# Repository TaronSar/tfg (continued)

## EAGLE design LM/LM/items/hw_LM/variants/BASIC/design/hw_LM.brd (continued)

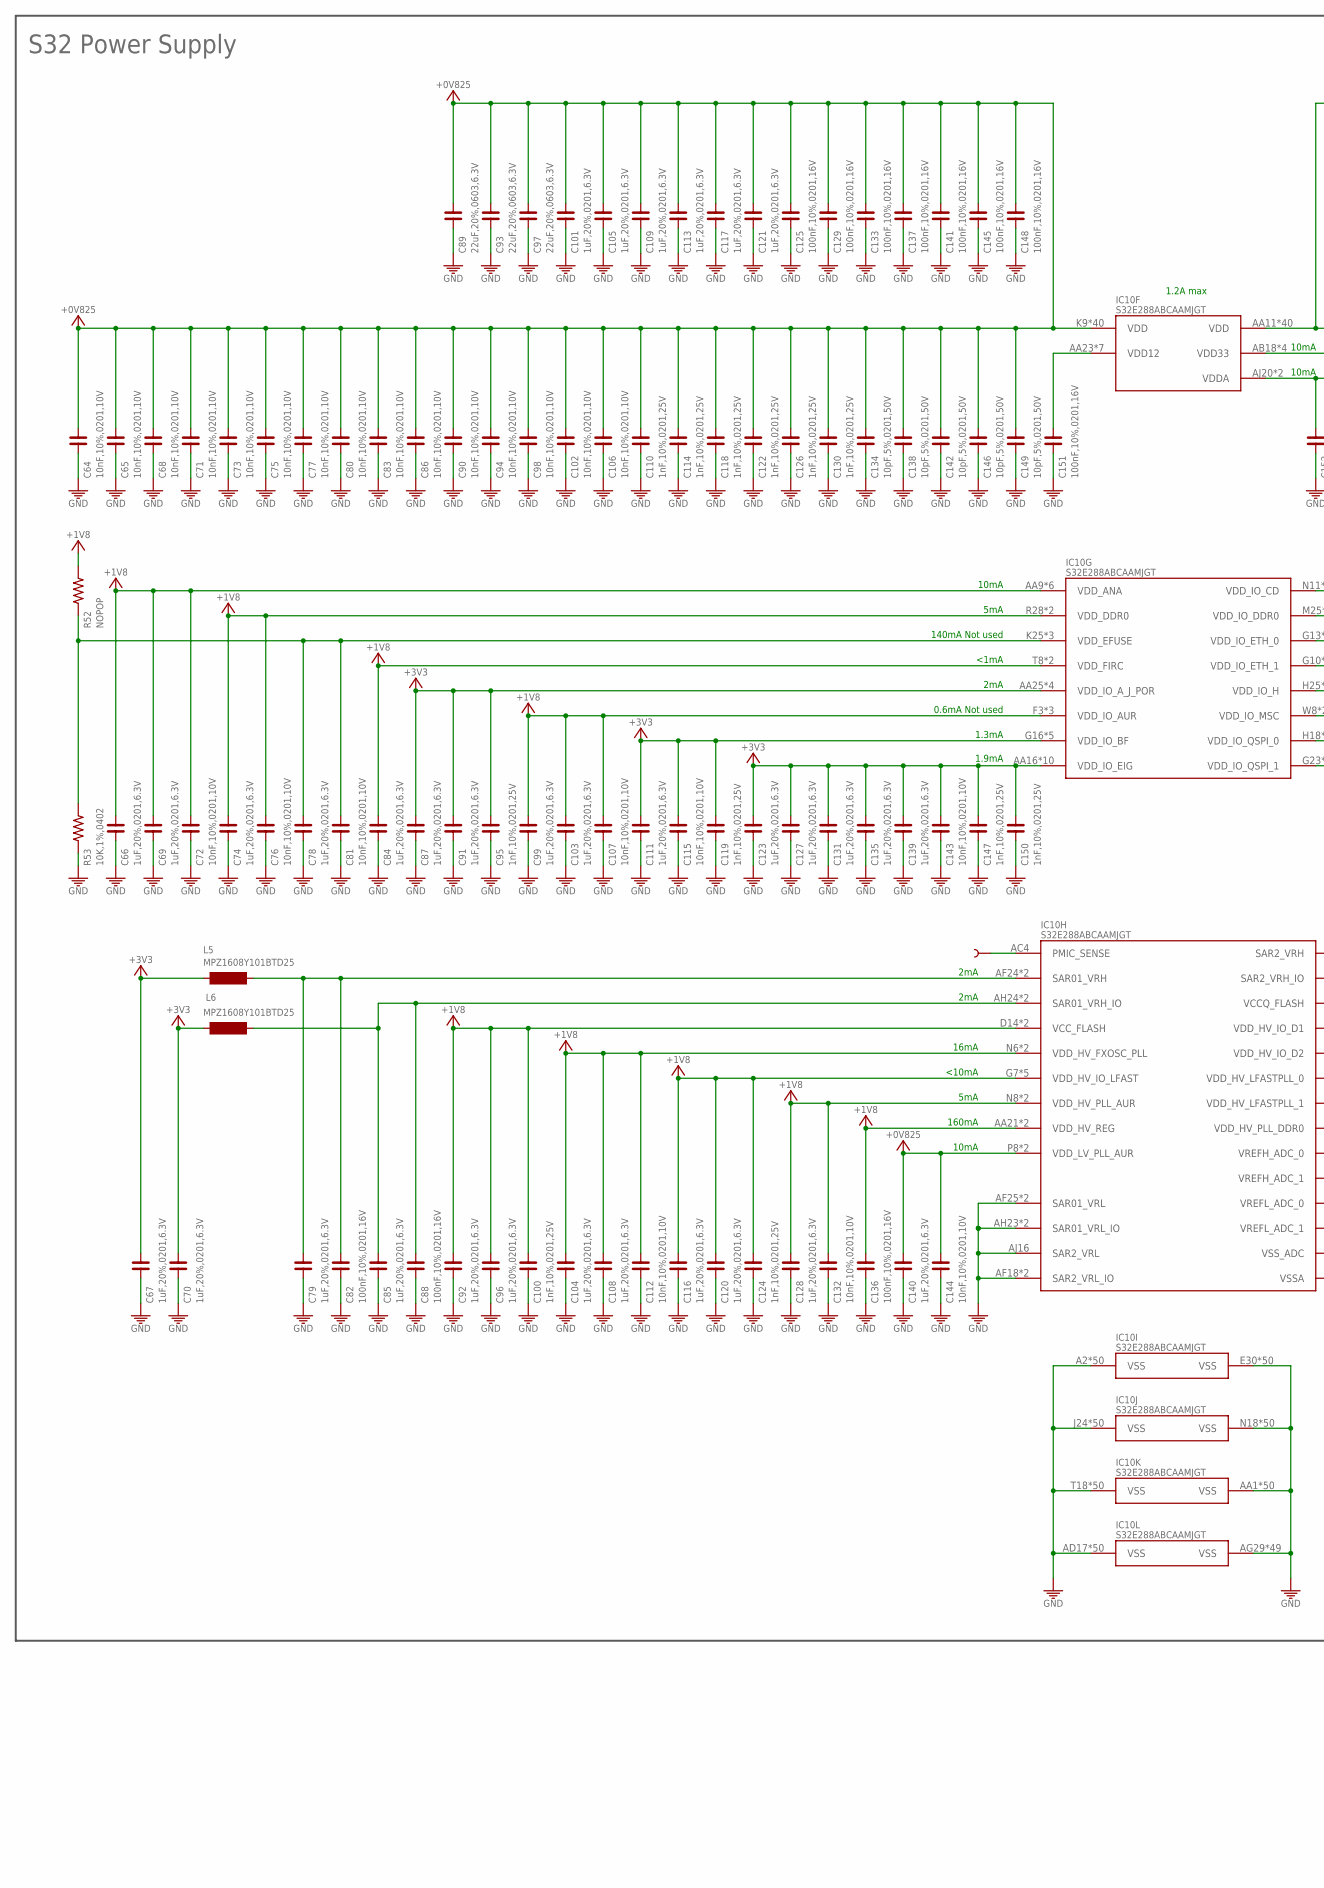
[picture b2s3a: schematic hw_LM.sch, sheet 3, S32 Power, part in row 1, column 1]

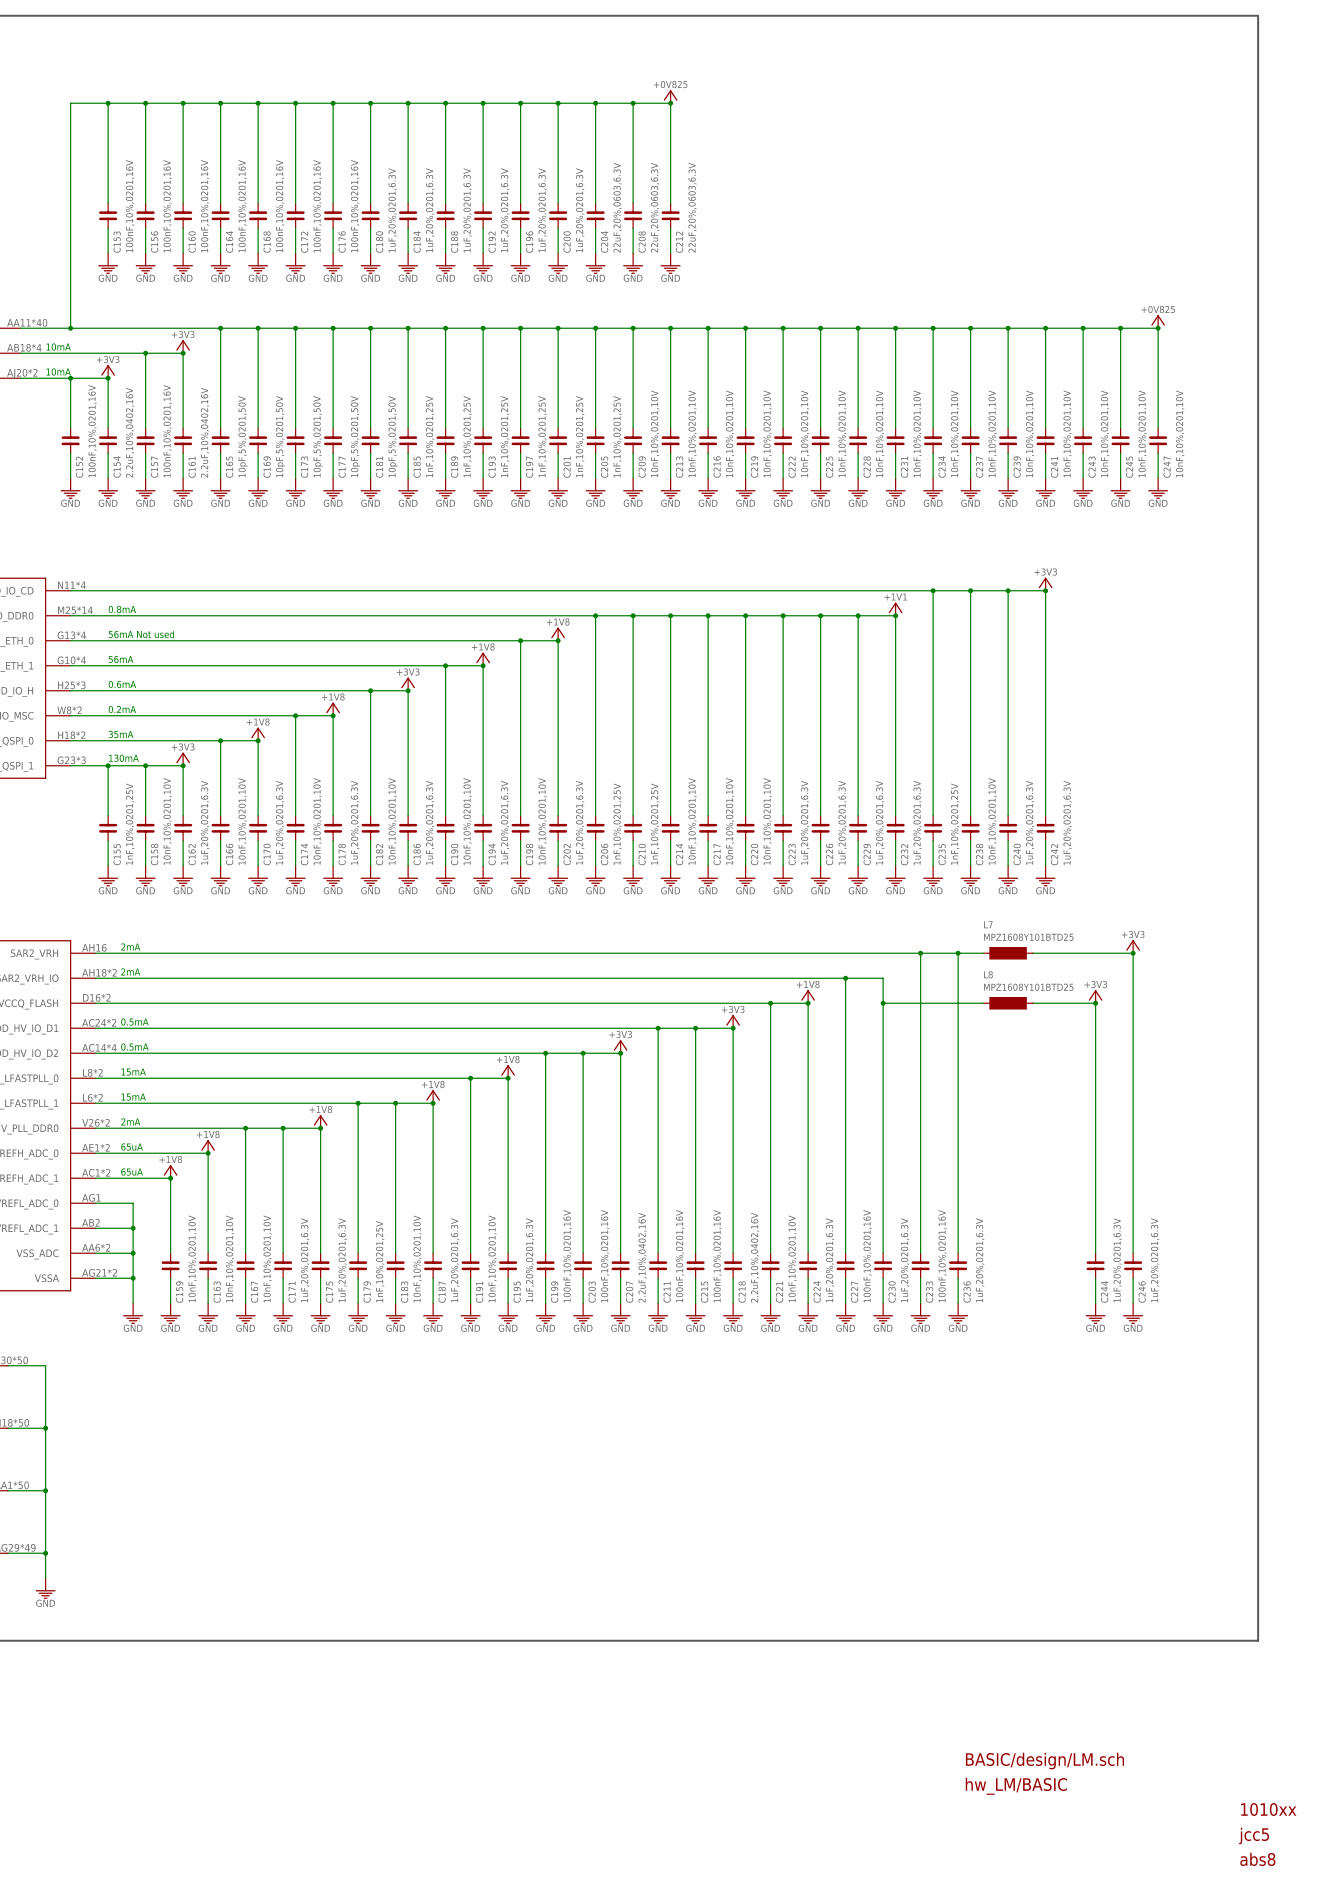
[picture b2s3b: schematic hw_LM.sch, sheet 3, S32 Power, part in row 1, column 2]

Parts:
C64, C65, C68, C71, C72, C73, C75, C76, C77, C80, C81, C83, C86, C90, C94, C98, C102, C106, C107, C112, C115, C132, C143, C144, C158, C159, C163, C166, C167, C174, C182, C183, C190, C191, C198, C209, C213, C214, C216, C217, C219, C220, C221, C222, C225, C228, C231, C234, C237, C238, C239, C241, C243, C245, C247: 10nF,10%,0201,10V; C0201
C66, C67, C69, C70, C74, C78, C79, C84, C85, C87, C91, C92, C96, C99, C101, C103, C104, C105, C108, C109, C111, C113, C116, C117, C120, C121, C123, C127, C128, C131, C135, C139, C140, C162, C170, C171, C175, C178, C180, C184, C186, C187, C188, C192, C194, C195, C196, C200, C202, C223, C224, C226, C229, C230, C232, C236, C240, C242, C244, C246: 1uF,20%,0201,6.3V; C0201
C82, C88, C125, C129, C133, C136, C137, C141, C145, C148, C151, C152, C153, C156, C157, C160, C164, C168, C172, C176, C199, C203, C211, C215, C227, C233: 100nF,10%,0201,16V; C0201
C89, C93, C97, C204, C208, C212: 22uF,20%,0603,6.3V; C0603
C95, C100, C110, C114, C118, C119, C122, C124, C126, C130, C147, C150, C155, C179, C185, C189, C193, C197, C201, C205, C206, C210, C235: 1nF,10%,0201,25V; C0201
C134, C138, C142, C146, C149, C165, C169, C173, C177, C181: 10pF,5%,0201,50V; C0201
C154, C161, C207, C218: 2.2uF,10%,0402,16V; C0402
IC10: S32E288ABCAAMJGT; IC_S32E288AACAAMJGR
L5, L6, L7, L8: MPZ1608Y101BTD25; L0603
R52: NOPOP; R0402
R53: 10K,1%,0402; R0402
TP2: NOPOP; PAD.02X.02

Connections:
+0V825: C64.1, C65.1, C68.1, C71.1, C73.1, C75.1, C77.1, C80.1, C83.1, C86.1, C89.2, C90.1, C93.2, C94.1, C97.2, C98.1, C101.1, C102.1, C105.1, C106.1, C109.1, C110.1, C113.1, C114.1, C117.1, C118.1, C121.1, C122.1, C125.1, C126.1, C129.1, C130.1, C133.1, C134.1, C137.1, C138.1, C140.1, C141.1, C142.1, C144.1, C145.1, C146.1, C148.1, C149.1, C153.1, C156.1, C160.1, C164.1, C165.1, C168.1, C169.1, C172.1, C173.1, C176.1, C177.1, C180.1, C181.1, C184.1, C185.1, C188.1, C189.1, C192.1, C193.1, C196.1, C197.1, C200.1, C201.1, C204.2, C205.1, C208.2, C209.1, C212.2, C213.1, C216.1, C219.1, C222.1, C225.1, C228.1, C231.1, C234.1, C237.1, C239.1, C241.1, C243.1, C245.1, C247.1, IC10.AA11 (VDD), IC10.AA12 (VDD), IC10.AA13 (VDD), IC10.AA14 (VDD), IC10.AA15 (VDD), IC10.AA18 (VDD), IC10.AA19 (VDD), IC10.AA20 (VDD), IC10.K9 (VDD), IC10.K10 (VDD), IC10.K11 (VDD), IC10.K12 (VDD), IC10.K13 (VDD), IC10.K14 (VDD), IC10.K15 (VDD), IC10.K16 (VDD), IC10.K17 (VDD), IC10.K18 (VDD), IC10.K19 (VDD), IC10.K20 (VDD), IC10.K21 (VDD), IC10.K22 (VDD), IC10.K23 (VDD), IC10.L10 (VDD), IC10.L11 (VDD), IC10.L12 (VDD), IC10.L13 (VDD), IC10.L14 (VDD), IC10.L15 (VDD), IC10.L16 (VDD), IC10.L17 (VDD), IC10.L18 (VDD), IC10.L19 (VDD), IC10.L20 (VDD), IC10.L21 (VDD), IC10.L22 (VDD), IC10.L23 (VDD), IC10.M10 (VDD), IC10.M11 (VDD), IC10.M22 (VDD), IC10.M23 (VDD), IC10.N22 (VDD), IC10.N23 (VDD), IC10.P8 (VDD_LV_PLL_AUR), IC10.P10 (VDD), IC10.P22 (VDD), IC10.P23 (VDD), IC10.R8 (VDD_LV_PLL_AUR), IC10.R10 (VDD), IC10.R11 (VDD), IC10.R22 (VDD), IC10.R23 (VDD), IC10.T10 (VDD), IC10.T11 (VDD), IC10.T22 (VDD), IC10.T23 (VDD), IC10.U10 (VDD), IC10.U11 (VDD), IC10.U22 (VDD), IC10.U23 (VDD), IC10.V10 (VDD), IC10.V11 (VDD), IC10.V22 (VDD), IC10.V23 (VDD), IC10.W10 (VDD), IC10.W11 (VDD), IC10.W22 (VDD), IC10.W23 (VDD), IC10.Y10 (VDD), IC10.Y11 (VDD), IC10.Y12 (VDD), IC10.Y13 (VDD), IC10.Y14 (VDD), IC10.Y15 (VDD), IC10.Y16 (VDD), IC10.Y17 (VDD), IC10.Y18 (VDD), IC10.Y19 (VDD), IC10.Y20 (VDD), IC10.Y21 (VDD), IC10.Y22 (VDD), IC10.Y23 (VDD); also elsewhere on the board
+1V1: C206.1, C210.1, C214.1, C217.1, C220.1, C223.1, C226.1, C229.1, C232.1, IC10.M25 (VDD_IO_DDR0), IC10.M27 (VDD_IO_DDR0), IC10.M28 (VDD_IO_DDR0), IC10.N25 (VDD_IO_DDR0), IC10.N27 (VDD_IO_DDR0), IC10.P25 (VDD_IO_DDR0), IC10.P27 (VDD_IO_DDR0), IC10.R25 (VDD_IO_DDR0), IC10.R27 (VDD_IO_DDR0), IC10.T25 (VDD_IO_DDR0), IC10.T27 (VDD_IO_DDR0), IC10.U25 (VDD_IO_DDR0), IC10.U27 (VDD_IO_DDR0), IC10.U28 (VDD_IO_DDR0); also elsewhere on the board
+1V8: C66.1, C69.1, C72.1, C74.1, C76.1, C84.1, C92.1, C96.1, C99.1, C100.1, C103.1, C104.1, C107.1, C108.1, C112.1, C116.1, C120.1, C124.1, C128.1, C132.1, C136.1, C159.1, C163.1, C166.1, C167.1, C170.1, C171.1, C174.1, C175.1, C178.1, C179.1, C183.1, C187.1, C190.1, C191.1, C194.1, C195.1, C198.1, C202.1, C221.1, C224.1, IC10.AA9 (VDD_ANA), IC10.AA10 (VDD_ANA), IC10.AA21 (VDD_HV_REG), IC10.AA22 (VDD_HV_REG), IC10.AB6 (VDD_ANA), IC10.AB7 (VDD_ANA), IC10.AC1 (VREFH_ADC_1), IC10.AD2 (VREFH_ADC_1), IC10.AE1 (VREFH_ADC_0), IC10.AF2 (VREFH_ADC_0), IC10.D14 (VCC_FLASH), IC10.D16 (VCCQ_FLASH), IC10.E14 (VCC_FLASH), IC10.E16 (VCCQ_FLASH), IC10.F3 (VDD_IO_AUR), IC10.G7 (VDD_HV_IO_LFAST), IC10.G10 (VDD_IO_ETH_1), IC10.G11 (VDD_IO_ETH_1), IC10.G13 (VDD_IO_ETH_0), IC10.G14 (VDD_IO_ETH_0), IC10.H6 (VDD_HV_IO_LFAST), IC10.H7 (VDD_HV_IO_LFAST), IC10.H8 (VDD_HV_IO_LFAST), IC10.H10 (VDD_IO_ETH_1), IC10.H11 (VDD_IO_ETH_1), IC10.H13 (VDD_IO_ETH_0), IC10.H14 (VDD_IO_ETH_0), IC10.H18 (VDD_IO_QSPI_0), IC10.H19 (VDD_IO_QSPI_0), IC10.J3 (VDD_IO_AUR), IC10.J6 (VDD_HV_IO_LFAST), IC10.L6 (VDD_HV_LFASTPLL_1), IC10.L8 (VDD_HV_LFASTPLL_0), IC10.M3 (VDD_IO_AUR), IC10.M6 (VDD_HV_LFASTPLL_1), IC10.M8 (VDD_HV_LFASTPLL_0), IC10.N6 (VDD_HV_FXOSC_PLL), IC10.N8 (VDD_HV_PLL_AUR), IC10.N9 (VDD_HV_PLL_AUR), IC10.P6 (VDD_HV_FXOSC_PLL), IC10.R28 (VDD_DDR0), IC10.T8 (VDD_FIRC), IC10.T28 (VDD_DDR0), IC10.U8 (VDD_FIRC), IC10.V7 (VDD_ANA), IC10.V26 (VDD_HV_PLL_DDR0), IC10.W6 (VDD_ANA), IC10.W8 (VDD_IO_MSC), IC10.W9 (VDD_IO_MSC), IC10.W26 (VDD_HV_PLL_DDR0), R52.2; also elsewhere on the board
+3V3: C67.1, C70.1, C87.1, C91.1, C95.1, C111.1, C115.1, C119.1, C123.1, C127.1, C131.1, C135.1, C139.1, C143.1, C147.1, C150.1, C152.1, C154.1, C155.1, C157.1, C158.1, C161.1, C162.1, C182.1, C186.1, C199.1, C203.1, C207.1, C211.1, C215.1, C218.1, C235.1, C238.1, C240.1, C242.1, C244.1, C246.1, IC10.AA16 (VDD_IO_EIG), IC10.AA17 (VDD_IO_EIG), IC10.AA25 (VDD_IO_A_J_POR), IC10.AB18 (VDD33), IC10.AB19 (VDD33), IC10.AB22 (VDD33), IC10.AB23 (VDD33), IC10.AC8 (VDD_IO_EIG), IC10.AC9 (VDD_IO_EIG), IC10.AC11 (VDD_IO_EIG), IC10.AC12 (VDD_IO_EIG), IC10.AC13 (VDD_IO_EIG), IC10.AC14 (VDD_HV_IO_D2), IC10.AC15 (VDD_HV_IO_D2), IC10.AC16 (VDD_HV_IO_D2), IC10.AC24 (VDD_HV_IO_D1), IC10.AD7 (VDD_IO_EIG), IC10.AD8 (VDD_IO_EIG), IC10.AD11 (VDD_IO_EIG), IC10.AD16 (VDD_HV_IO_D2), IC10.AD24 (VDD_HV_IO_D1), IC10.AJ20 (VDDA), IC10.AJ21 (VDDA), IC10.G16 (VDD_IO_BF), IC10.G17 (VDD_IO_BF), IC10.G20 (VDD_IO_BF), IC10.G21 (VDD_IO_BF), IC10.G23 (VDD_IO_QSPI_1), IC10.G24 (VDD_IO_QSPI_1), IC10.H16 (VDD_IO_BF), IC10.H22 (VDD_IO_QSPI_1), IC10.H25 (VDD_IO_H), IC10.H26 (VDD_IO_H), IC10.H27 (VDD_IO_H), IC10.N11 (VDD_IO_CD), IC10.P11 (VDD_IO_CD), IC10.T6 (VDD_IO_CD), IC10.U6 (VDD_IO_CD), IC10.W28 (VDD_IO_A_J_POR), IC10.Y25 (VDD_IO_A_J_POR), IC10.Y27 (VDD_IO_A_J_POR), L5.1, L6.1, L7.1, L8.1; also elsewhere on the board
GND: C64.2, C65.2, C66.2, C67.2, C68.2, C69.2, C70.2, C71.2, C72.2, C73.2, C74.2, C75.2, C76.2, C77.2, C78.2, C79.2, C80.2, C81.2, C82.2, C83.2, C84.2, C85.2, C86.2, C87.2, C88.2, C89.1, C90.2, C91.2, C92.2, C93.1, C94.2, C95.2, C96.2, C97.1, C98.2, C99.2, C100.2, C101.2, C102.2, C103.2, C104.2, C105.2, C106.2, C107.2, C108.2, C109.2, C110.2, C111.2, C112.2, C113.2, C114.2, C115.2, C116.2, C117.2, C118.2, C119.2, C120.2, C121.2, C122.2, C123.2, C124.2, C125.2, C126.2, C127.2, C128.2, C129.2, C130.2, C131.2, C132.2, C133.2, C134.2, C135.2, C136.2, C137.2, C138.2, C139.2, C140.2, C141.2, C142.2, C143.2, C144.2, C145.2, C146.2, C147.2, C148.2, C149.2, C150.2, C151.2, C152.2, C153.2, C154.2, C155.2, C156.2, C157.2, C158.2, C159.2, C160.2, C161.2, C162.2, C163.2, C164.2, C165.2, C166.2, C167.2, C168.2, C169.2, C170.2, C171.2, C172.2, C173.2, C174.2, C175.2, C176.2, C177.2, C178.2, C179.2, C180.2, C181.2, C182.2, C183.2, C184.2, C185.2, C186.2, C187.2, C188.2, C189.2, C190.2, C191.2, C192.2, C193.2, C194.2, C195.2, C196.2, C197.2, C198.2, C199.2, C200.2, C201.2, C202.2, C203.2, C204.1, C205.2, C206.2, C207.2, C208.1, C209.2, C210.2, C211.2, C212.1, C213.2, C214.2, C215.2, C216.2, C217.2, C218.2, C219.2, C220.2, C221.2, C222.2, C223.2, C224.2, C225.2, C226.2, C227.2, C228.2, C229.2, C230.2, C231.2, C232.2, C233.2, C234.2, C235.2, C236.2, C237.2, C238.2, C239.2, C240.2, C241.2, C242.2, C243.2, C244.2, C245.2, C246.2, C247.2, IC10.A2 (VSS), IC10.A31 (VSS), IC10.AA1 (VSS), IC10.AA2 (VSS), IC10.AA3 (VSS), IC10.AA6 (VSS_ADC), IC10.AA8 (VSS_ADC), IC10.AA24 (VSS), IC10.AA26 (VSS), IC10.AA27 (VSS), IC10.AA28 (VSS), IC10.AA29 (VSS), IC10.AA30 (VSS), IC10.AA31 (VSS), IC10.AB2 (VREFL_ADC_1), IC10.AB3 (VSS), IC10.AB4 (VSS), IC10.AB5 (VSS), IC10.AB9 (VSS), IC10.AB11 (VSS), IC10.AB13 (VSS), IC10.AB15 (VSS), IC10.AB17 (VSS), IC10.AB20 (VSS), IC10.AB21 (VSS), IC10.AB25 (VSS), IC10.AB30 (VSS), IC10.AC3 (VSS), IC10.AC6 (VSS), IC10.AC7 (VSS), IC10.AC10 (VSS), IC10.AC19 (VSS), IC10.AC20 (VSS), IC10.AC21 (VSS), IC10.AC22 (VSS), IC10.AC23 (VSS), IC10.AC30 (VSS), IC10.AD3 (VSS), IC10.AD6 (VSS), IC10.AD9 (VSS), IC10.AD12 (VSS), IC10.AD15 (VSS), IC10.AD17 (VSS), IC10.AD19 (VSS), IC10.AD20 (VSS), IC10.AD21 (VSS), IC10.AD22 (VSS), IC10.AD23 (VSS), IC10.AD25 (VSS), IC10.AD26 (VSS), IC10.AD27 (VSS), IC10.AD28 (VSS), IC10.AD29 (VSS), IC10.AD30 (VSS), IC10.AE3 (VSS), IC10.AE4 (VSS), IC10.AE5 (VSS), IC10.AE9 (VSS), IC10.AE12 (VSS), IC10.AE15 (VSS), IC10.AE19 (VSS), IC10.AE20 (VSS), IC10.AE21 (VSS), IC10.AE22 (VSS), IC10.AE23 (VSS), IC10.AE30 (VSS), IC10.AF3 (VSS), IC10.AF9 (VSS), IC10.AF12 (VSS), IC10.AF15 (VSS), IC10.AF17 (VSS), IC10.AF18 (SAR2_VRL_IO), IC10.AF19 (VSS), IC10.AF20 (VSS), IC10.AF21 (VSS), IC10.AF22 (VSS), IC10.AF23 (VSS), IC10.AF25 (SAR01_VRL), IC10.AF26 (VSS), IC10.AF30 (VSS), IC10.AG1 (VREFL_ADC_0), IC10.AG3 (VSS), IC10.AG4 (VSS), IC10.AG5 (VSS), IC10.AG6 (VSS), IC10.AG9 (VSS), IC10.AG12 (VSS), IC10.AG15 (VSS), IC10.AG16 (VSS), IC10.AG18 (SAR2_VRL_IO), IC10.AG19 (VSS), IC10.AG20 (VSS), IC10.AG21 (VSSA), IC10.AG22 (VSS), IC10.AG23 (VSS), IC10.AG26 (SAR01_VRL), IC10.AG27 (VSS), IC10.AG28 (VSS), IC10.AG29 (VSS), IC10.AG30 (VSS), IC10.AH1 (VSS), IC10.AH2 (VSS), IC10.AH3 (VSS), IC10.AH6 (VSS), IC10.AH9 (VSS), IC10.AH12 (VSS), IC10.AH15 (VSS), IC10.AH17 (VSS), IC10.AH19 (VSS), IC10.AH20 (VSS), IC10.AH21 (VSSA), IC10.AH22 (VSS), IC10.AH23 (SAR01_VRL_IO), IC10.AH25 (VSS), IC10.AH26 (VSS), IC10.AH30 (VSS), IC10.AJ3 (VSS), IC10.AJ6 (VSS), IC10.AJ9 (VSS), IC10.AJ12 (VSS), IC10.AJ15 (VSS), IC10.AJ16 (SAR2_VRL), IC10.AJ23 (SAR01_VRL_IO), IC10.AJ30 (VSS), IC10.AK3 (VSS), IC10.AK4 (VSS), IC10.AK5 (VSS), IC10.AK6 (VSS), IC10.AK7 (VSS), IC10.AK8 (VSS), IC10.AK9 (VSS), IC10.AK10 (VSS), IC10.AK11 (VSS), IC10.AK12 (VSS), IC10.AK13 (VSS), IC10.AK14 (VSS), IC10.AK15 (VSS), IC10.AK16 (VSS), IC10.AK17 (VSS), IC10.AK19 (VSS), IC10.AK21 (VSS), IC10.AK23 (VSS), IC10.AK25 (VSS), IC10.AK26 (VSS), IC10.AK27 (VSS), IC10.AK28 (VSS), IC10.AK29 (VSS), IC10.AL1 (VSS), IC10.AL32 (VSS), IC10.AM2 (VSS), IC10.AM31 (VSS), IC10.B1 (VSS), IC10.B32 (VSS), IC10.C3 (VSS), IC10.C4 (VSS), IC10.C5 (VSS), IC10.C6 (VSS), IC10.C7 (VSS), IC10.C8 (VSS), IC10.C9 (VSS), IC10.C10 (VSS), IC10.C11 (VSS), IC10.C12 (VSS), IC10.C13 (VSS), IC10.C14 (VSS), IC10.C15 (VSS), IC10.C16 (VSS), IC10.C17 (VSS), IC10.C18 (VSS), IC10.C19 (VSS), IC10.C20 (VSS), IC10.C21 (VSS), IC10.C22 (VSS), IC10.C23 (VSS), IC10.C24 (VSS), IC10.C25 (VSS), IC10.C26 (VSS), IC10.C27 (VSS), IC10.C28 (VSS), IC10.C29 (VSS), IC10.D3 (VSS), IC10.D6 (VSS), IC10.D9 (VSS), IC10.D12 (VSS), IC10.D15 (VSS), IC10.D18 (VSS), IC10.D21 (VSS), IC10.D24 (VSS), IC10.D27 (VSS), IC10.D30 (VSS), IC10.E3 (VSS), IC10.E6 (VSS), IC10.E9 (VSS), IC10.E12 (VSS), IC10.E15 (VSS), IC10.E18 (VSS), IC10.E21 (VSS), IC10.E24 (VSS), IC10.E27 (VSS), IC10.E30 (VSS), IC10.F1 (VSS), IC10.F2 (VSS), IC10.F4 (VSS), IC10.F5 (VSS), IC10.F6 (VSS), IC10.F7 (VSS), IC10.F9 (VSS), IC10.F12 (VSS), IC10.F15 (VSS), IC10.F18 (VSS), IC10.F21 (VSS), IC10.F24 (VSS), IC10.F27 (VSS), IC10.F28 (VSS), IC10.F29 (VSS), IC10.F30 (VSS), IC10.F31 (VSS), IC10.G3 (VSS), IC10.G8 (VSS), IC10.G9 (VSS), IC10.G12 (VSS), IC10.G15 (VSS), IC10.G18 (VSS), IC10.G19 (VSS), IC10.G22 (VSS), IC10.G25 (VSS), IC10.G26 (VSS), IC10.G27 (VSS), IC10.G29 (VSS), IC10.H3 (VSS), IC10.H9 (VSS), IC10.H12 (VSS), IC10.H15 (VSS), IC10.H17 (VSS), IC10.H20 (VSS), IC10.H21 (VSS), IC10.H23 (VSS), IC10.H24 (VSS), IC10.H29 (VSS), IC10.J1 (VSS), IC10.J2 (VSS), IC10.J8 (VSS), IC10.J10 (VSS), IC10.J12 (VSS), IC10.J14 (VSS), IC10.J16 (VSS), IC10.J18 (VSS), IC10.J20 (VSS), IC10.J22 (VSS), IC10.J24 (VSS), IC10.J25 (VSS), IC10.J26 (VSS), IC10.J27 (VSS), IC10.J28 (VSS), IC10.J29 (VSS), IC10.J30 (VSS), IC10.J31 (VSS), IC10.K3 (VSS), IC10.K4 (VSS), IC10.K5 (VSS), IC10.K6 (VSS), IC10.K7 (VSS), IC10.K8 (VSS)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; also elsewhere on the board
PMIC_SENSE: IC10.AC4 (PMIC_SENSE), TP2.P$1
SAR01_VRH: C79.1, C82.1, IC10.AF24 (SAR01_VRH), IC10.AG24 (SAR01_VRH), L5.2
SAR01_VRH_IO: C85.1, C88.1, IC10.AH24 (SAR01_VRH_IO), IC10.AJ24 (SAR01_VRH_IO), L6.2
SAR2_VRH: C233.1, C236.1, IC10.AH16 (SAR2_VRH), L7.2
SAR2_VRH_IO: C227.1, C230.1, IC10.AH18 (SAR2_VRH_IO), IC10.AJ18 (SAR2_VRH_IO), L8.2
VDD12: C151.1, IC10.AA23 (VDD12), IC10.AC18 (VDD12), IC10.AD18 (VDD12), IC10.AE18 (VDD12), IC10.AE24 (VDD12), IC10.AJ19 (VDD12), IC10.AJ22 (VDD12)
VDD_EFUSE: C78.1, C81.1, IC10.K25 (VDD_EFUSE), IC10.K26 (VDD_EFUSE), IC10.K27 (VDD_EFUSE), R52.1, R53.2

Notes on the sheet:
S32 Power Supply
10mA
2mA
65uA
5mA
1.2A max
16mA
<10mA
160mA
0.5mA
15mA
<1mA
0.6mA Not used
0.8mA
1.3mA
1.9mA
56mA Not used
56mA
0.6mA
0.2mA
35mA
130mA
BASIC/design/LM.sch
hw_LM/BASIC
1010xx
jcc5
abs8
140mA Not used

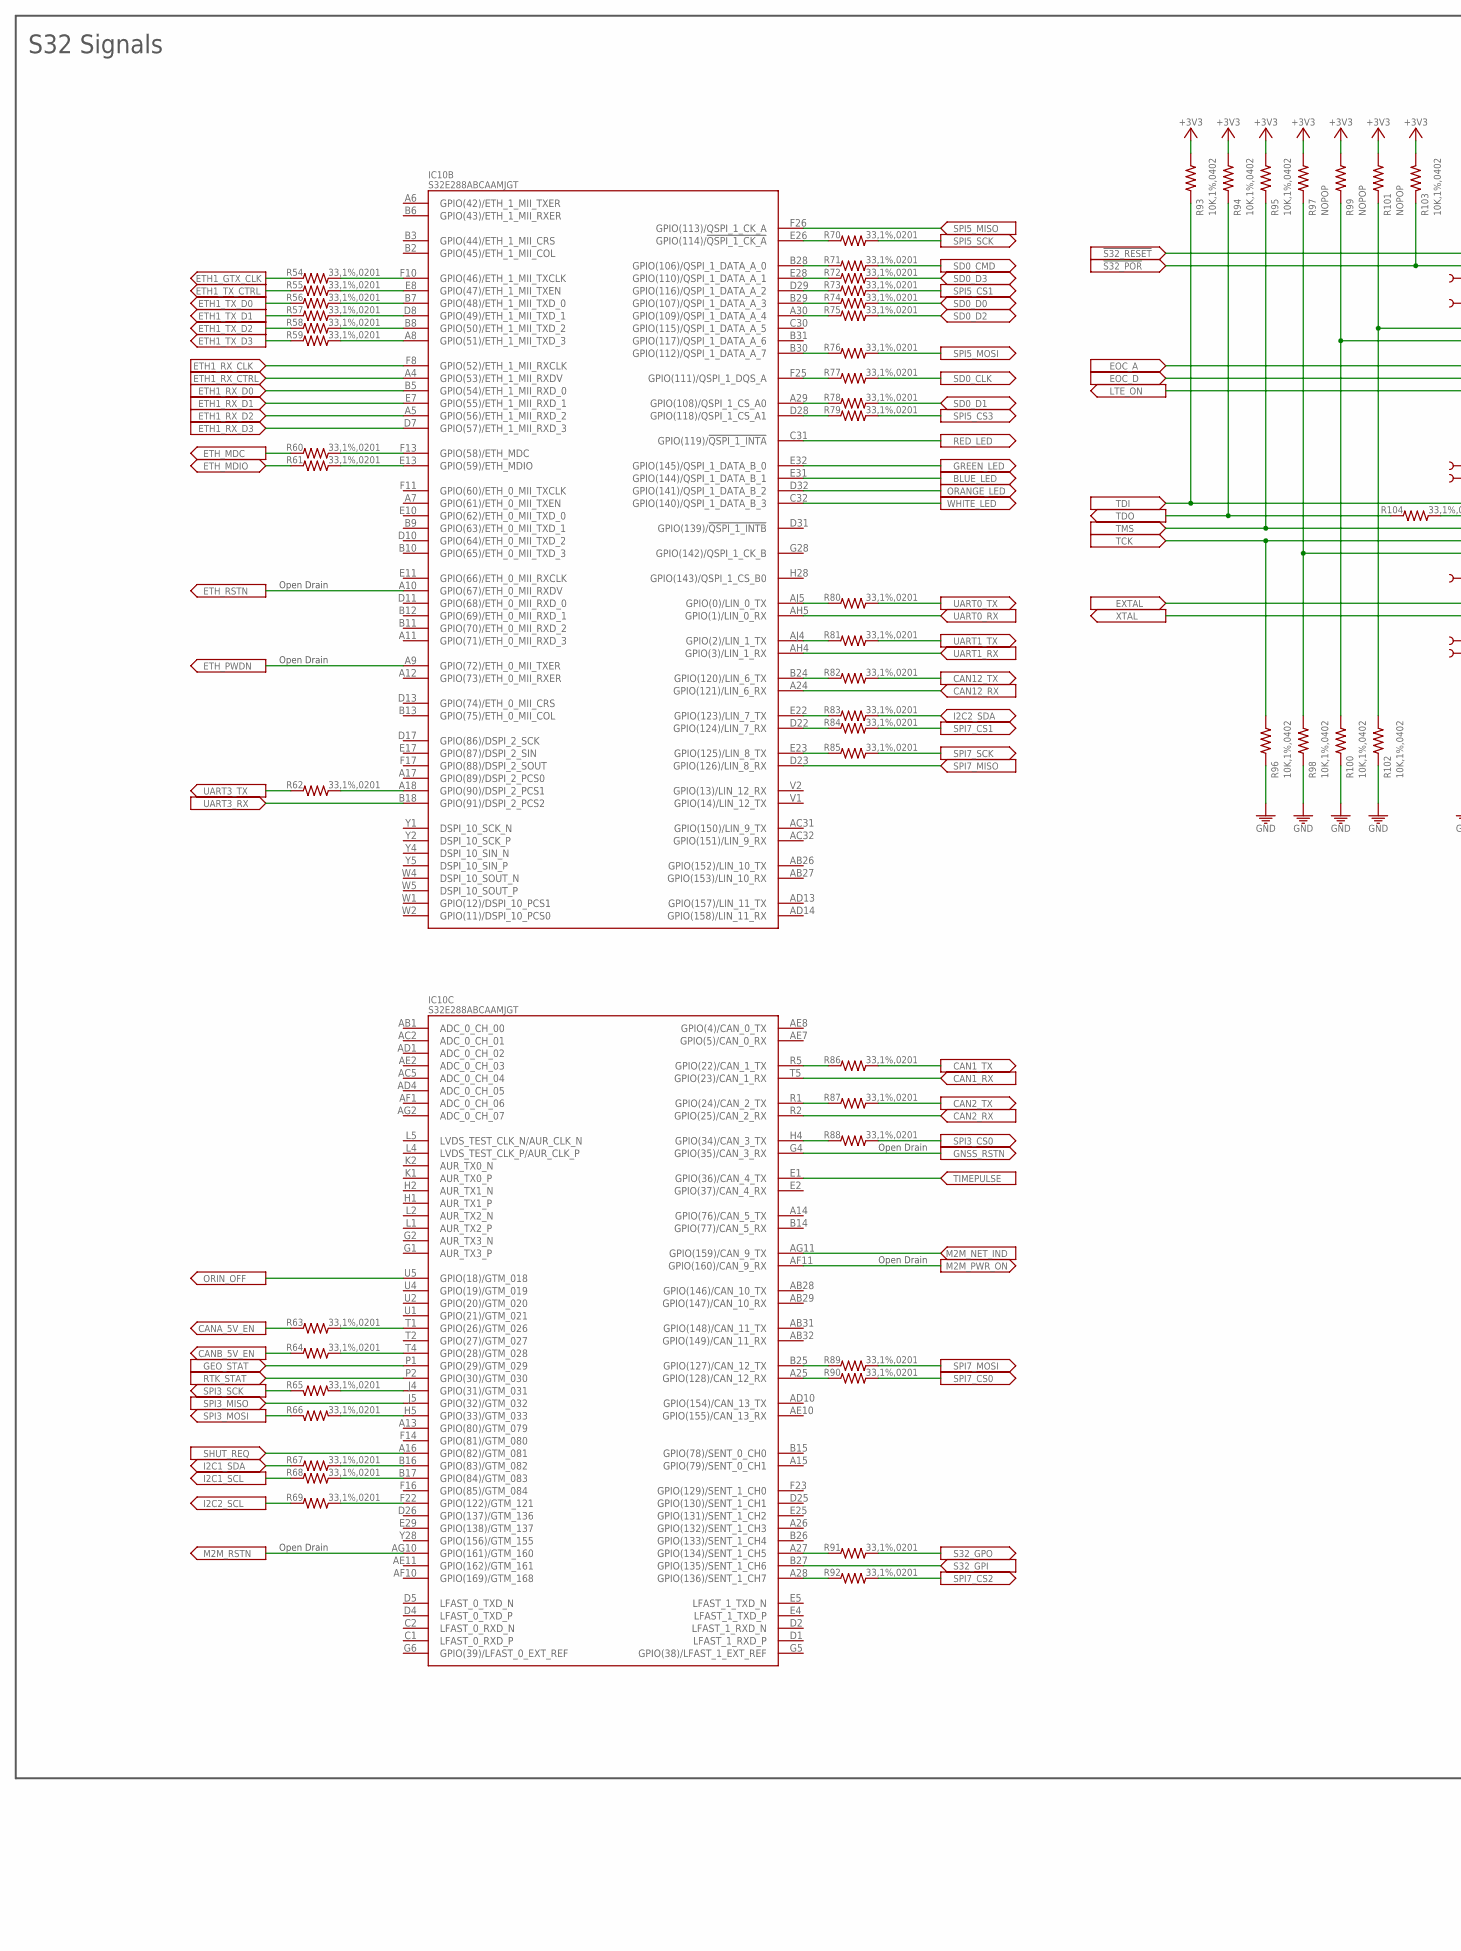
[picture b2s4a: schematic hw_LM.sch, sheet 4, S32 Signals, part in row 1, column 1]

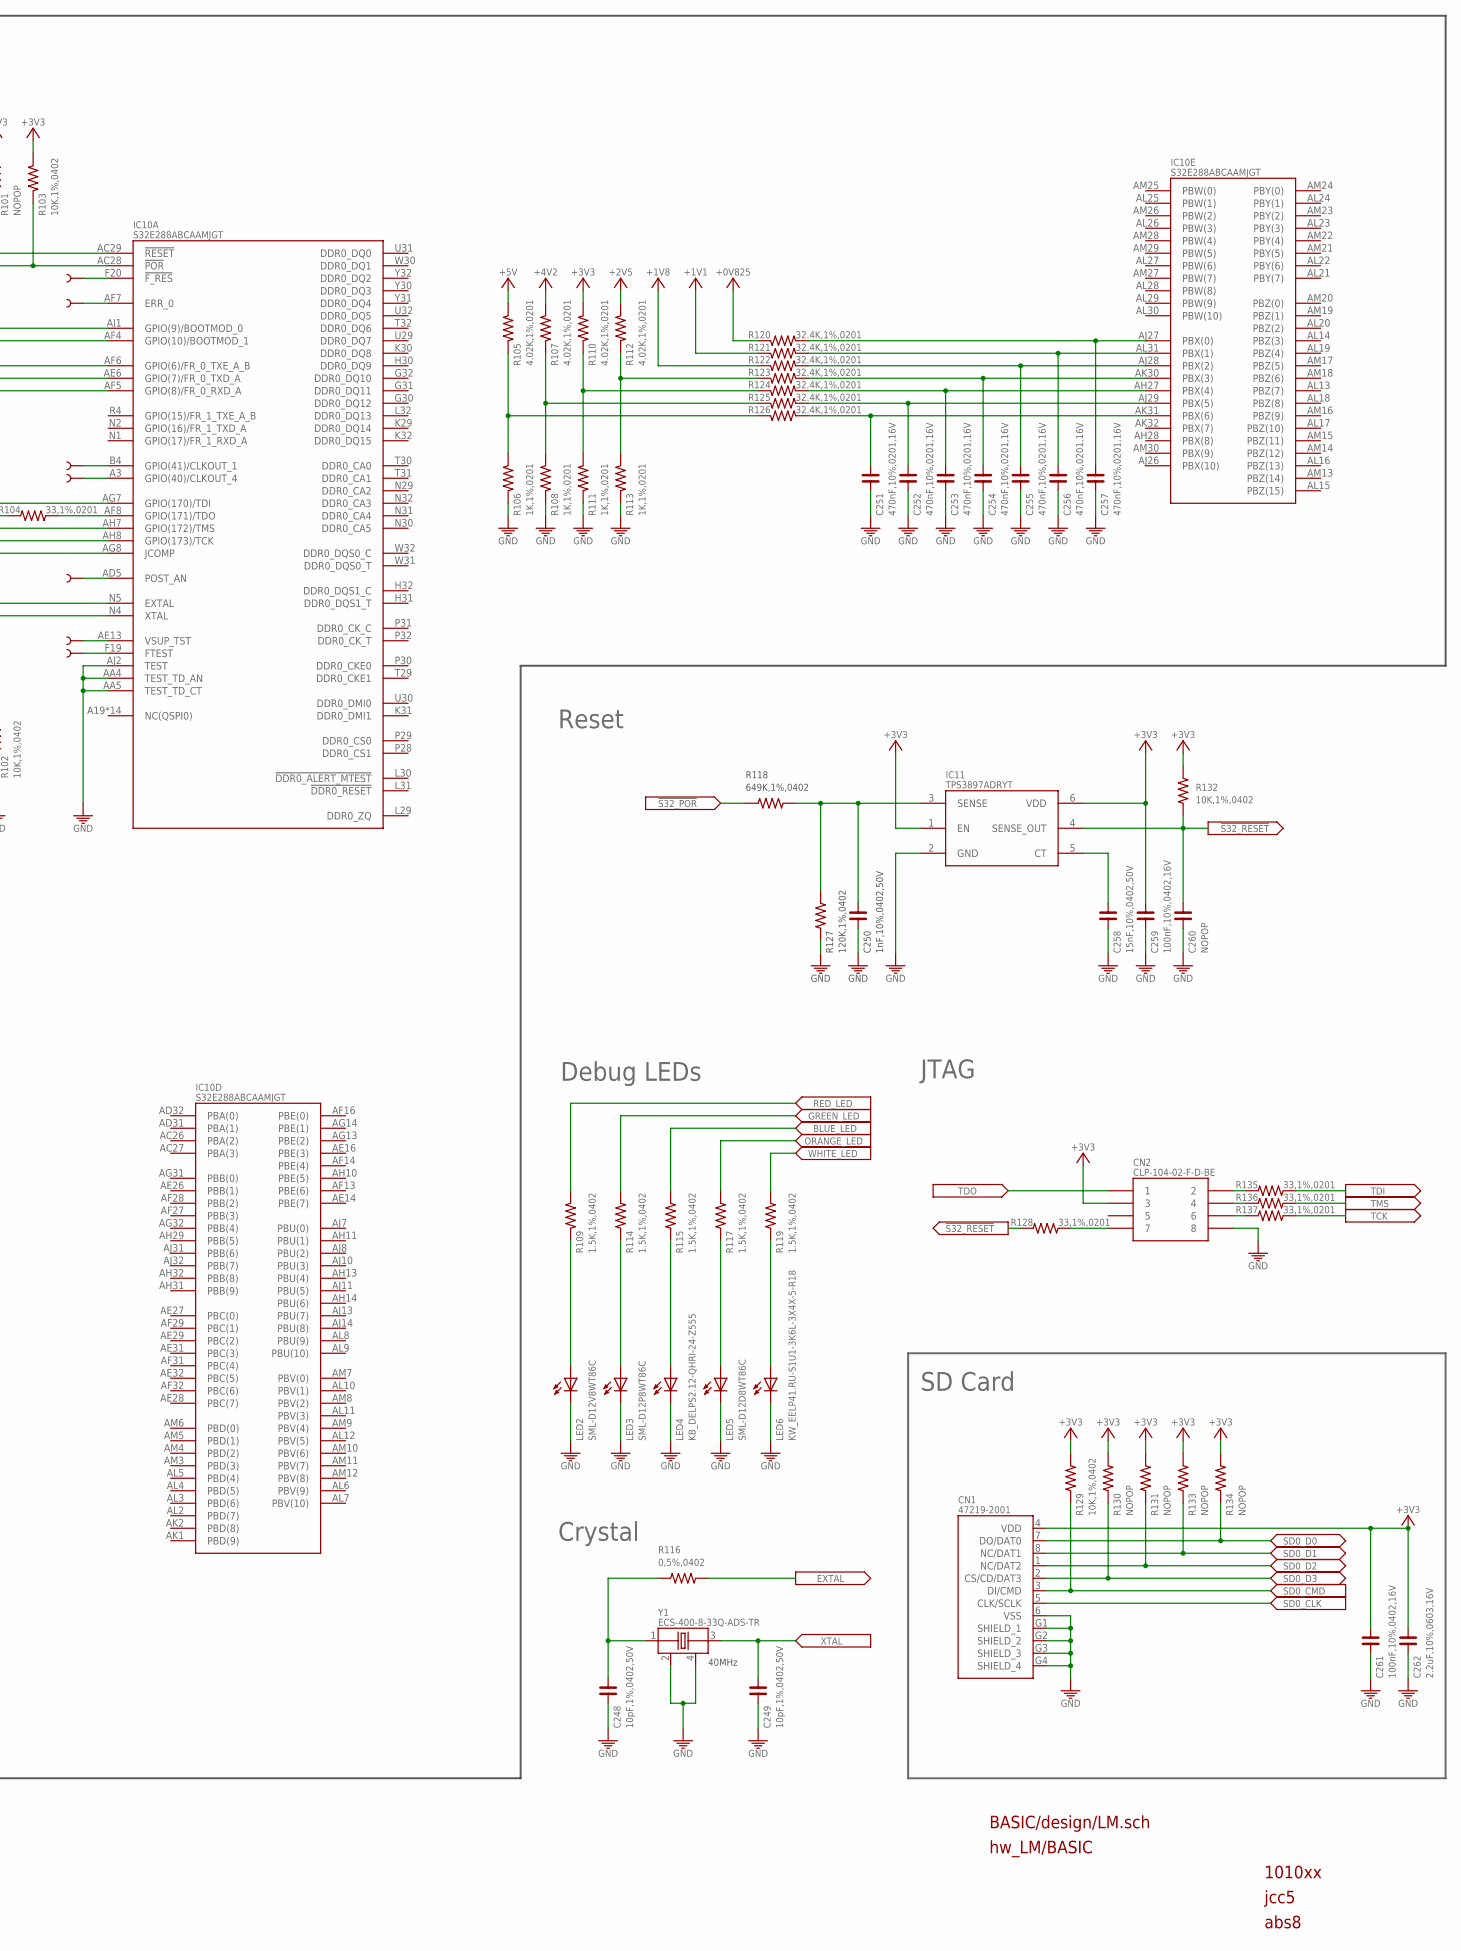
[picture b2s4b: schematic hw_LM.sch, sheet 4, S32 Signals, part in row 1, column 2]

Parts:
C248, C249: 10pF,1%,0402,50V; C0402
C250: 1nF,10%,0402,50V; C0402
C251, C252, C253, C254, C255, C256, C257: 470nF,10%,0201,16V; C0201
C258: 15nF,10%,0402,50V; C0402
C259, C261: 100nF,10%,0402,16V; C0402
C260: NOPOP; C0402
C262: 2.2uF,10%,0603,16V; C0603
CN1: 47219-2001; SD-LATCH
CN2: CLP-104-02-F-D-BE; CLP-104-02-X-D-BE
IC10: S32E288ABCAAMJGT; IC_S32E288AACAAMJGR
IC11: TPS3897ADRYT; USON6
LED2: SML-D12V8WT86C; LED-0603
LED3: SML-D12P8WT86C; LED-0603
LED4: KB_DELPS2.12-QHRI-24-Z555; LED-0603
LED5: SML-D12D8WT86C; LED-0603
LED6: KW_EELP41.RU-S1U1-3K6L-3X4X-5-R18; LED-0603
R54, R55, R56, R57, R58, R59, R60, R61, R62, R63, R64, R65, R66, R67, R68, R69, R70, R71, R72, R73, R74, R75, R76, R77, R78, R79, R80, R81, R82, R83, R84, R85, R86, R87, R88, R89, R90, R91, R92, R104, R128, R135, R136, R137: 33,1%,0201; R0201
R93, R94, R95, R96, R98, R100, R102, R103, R129, R132: 10K,1%,0402; R0402
R97, R99, R101, R130, R131, R133, R134: NOPOP; R0402
R105, R107, R110, R112: 4.02K,1%,0201; R0201
R106, R108, R111, R113: 1K,1%,0201; R0201
R109, R114, R115, R117, R119: 1.5K,1%,0402; R0402
R116: 0,5%,0402; R0402
R118: 649K,1%,0402; R0402
R120, R121, R122, R123, R124, R125, R126: 32.4K,1%,0201; R0201
R127: 120K,1%,0402; R0402
TP3, TP4, TP5, TP6, TP7, TP8, TP9: NOPOP; PAD.02X.02
Y1: ECS-400-8-33Q-ADS-TR; ECS-250-18-33Q-DS-TR3

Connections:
0V825_ADC: C257.1, IC10.AJ27 (PBX(0)), R120.2
1V1_ADC: C256.1, IC10.AL31 (PBX(1)), R121.2
1V8_ADC: C255.1, IC10.AJ28 (PBX(2)), R122.2
2V5_ADC: C254.1, IC10.AK30 (PBX(3)), R123.2
3V3_ADC: C253.1, IC10.AH27 (PBX(4)), R124.2
4V2_ADC: C252.1, IC10.AJ29 (PBX(5)), R125.2
5V_ADC: C251.1, IC10.AK31 (PBX(6)), R126.2
!F_RES: IC10.F20 (!F_RES), TP3.P$1
!S32_POR: IC10.AC28 (!POR), R103.1, R118.1; also elsewhere on the board
!S32_RESET: C260.1, IC10.AC29 (!RESET), IC11.4 (SENSE_OUT), R128.1, R132.1
+0V825: R120.1; also elsewhere on the board
+1V1: R121.1; also elsewhere on the board
+1V8: R122.1; also elsewhere on the board
+2V5: R112.1; also elsewhere on the board
+3V3: C259.1, C261.1, C262.1, CN1.4 (VDD), CN2.3, IC11.1 (EN), IC11.6 (VDD), R93.2, R94.2, R95.2, R97.2, R99.2, R101.2, R103.2, R110.1, R129.2, R130.2, R131.2, R132.2, R133.2, R134.2; also elsewhere on the board
+4V2: R107.1; also elsewhere on the board
+5V: R105.1; also elsewhere on the board
BLUE_LED: IC10.E31 (GPIO(144)/QSPI_1_DATA_B_1), R115.1
BOOTMOD_0: IC10.AJ1 (GPIO(9)/BOOTMOD_0), R101.1, R102.2
BOOTMOD_1: IC10.AF4 (GPIO(10)/BOOTMOD_1), R99.1, R100.2
CAN1_RX: IC10.T5 (GPIO(23)/CAN_1_RX); also elsewhere on the board
CAN1_TX: R86.2; also elsewhere on the board
CAN2_RX: IC10.R2 (GPIO(25)/CAN_2_RX); also elsewhere on the board
CAN2_TX: R87.2; also elsewhere on the board
CAN12_RX: IC10.A24 (GPIO(121)/LIN_6_RX); also elsewhere on the board
CAN12_TX: R82.2; also elsewhere on the board
CANA_5V_EN: R63.1; also elsewhere on the board
CANB_5V_EN: R64.1; also elsewhere on the board
CLKOUT_1: IC10.B4 (GPIO(41)/CLKOUT_1), TP5.P$1
CLKOUT_4: IC10.A3 (GPIO(40)/CLKOUT_4), TP6.P$1
EOC_A: IC10.AF6 (GPIO(6)/FR_0_TXE_A_B); also elsewhere on the board
EOC_D: IC10.AE6 (GPIO(7)/FR_0_TXD_A); also elsewhere on the board
ERR_0: IC10.AF7 (ERR_0), TP4.P$1
ETH1_GTX_CLK: R54.1; also elsewhere on the board
ETH1_RX_CLK: IC10.F8 (GPIO(52)/ETH_1_MII_RXCLK); also elsewhere on the board
ETH1_RX_CTRL: IC10.A4 (GPIO(53)/ETH_1_MII_RXDV); also elsewhere on the board
ETH1_RX_D0: IC10.B5 (GPIO(54)/ETH_1_MII_RXD_0); also elsewhere on the board
ETH1_RX_D1: IC10.E7 (GPIO(55)/ETH_1_MII_RXD_1); also elsewhere on the board
ETH1_RX_D2: IC10.A5 (GPIO(56)/ETH_1_MII_RXD_2); also elsewhere on the board
ETH1_RX_D3: IC10.D7 (GPIO(57)/ETH_1_MII_RXD_3); also elsewhere on the board
ETH1_TX_CTRL: R55.1; also elsewhere on the board
ETH1_TX_D0: R56.1; also elsewhere on the board
ETH1_TX_D1: R57.1; also elsewhere on the board
ETH1_TX_D2: R58.1; also elsewhere on the board
ETH1_TX_D3: R59.1; also elsewhere on the board
ETH_MDC: R60.1; also elsewhere on the board
ETH_MDIO: R61.1; also elsewhere on the board
ETH_PWDN: IC10.A9 (GPIO(72)/ETH_0_MII_TXER); also elsewhere on the board
ETH_RSTN: IC10.A10 (GPIO(67)/ETH_0_MII_RXDV); also elsewhere on the board
EXTAL: IC10.N5 (EXTAL), R116.2
FTEST: IC10.F19 (FTEST), TP9.P$1
GEO_STAT: IC10.P1 (GPIO(29)/GTM_029); also elsewhere on the board
GND: C248.2, C249.2, C250.2, C251.2, C252.2, C253.2, C254.2, C255.2, C256.2, C257.2, C258.2, C259.2, C260.2, C261.2, C262.2, CN1.6 (VSS), CN1.G1 (SHIELD_1), CN1.G2 (SHIELD_2), CN1.G3 (SHIELD_3), CN1.G4 (SHIELD_4), CN2.8, IC10.AA4 (TEST_TD_AN), IC10.AA5 (TEST_TD_CT), IC10.AJ2 (TEST), IC11.2 (GND), LED2.C, LED3.C, LED4.C, LED5.C, LED6.C, R96.1, R98.1, R100.1, R102.1, R106.1, R108.1, R111.1, R113.1, R127.2, Y1.2 (GND_2), Y1.4 (GND_4); also elsewhere on the board
GNSS_RSTN: IC10.G4 (GPIO(35)/CAN_3_RX); also elsewhere on the board
GPIO0: IC10.AJ5 (GPIO(0)/LIN_0_TX), R80.1
GPIO2: IC10.AJ4 (GPIO(2)/LIN_1_TX), R81.1
GPIO22: IC10.R5 (GPIO(22)/CAN_1_TX), R86.1
GPIO24: IC10.R1 (GPIO(24)/CAN_2_TX), R87.1
GPIO26: IC10.T1 (GPIO(26)/GTM_026), R63.2
GPIO28: IC10.T4 (GPIO(28)/GTM_028), R64.2
GPIO31: IC10.J4 (GPIO(31)/GTM_031), R65.2
GPIO33: IC10.H5 (GPIO(33)/GTM_033), R66.2
GPIO34: IC10.H4 (GPIO(34)/CAN_3_TX), R88.1
GPIO46: IC10.F10 (GPIO(46)/ETH_1_MII_TXCLK), R54.2
GPIO47: IC10.E8 (GPIO(47)/ETH_1_MII_TXEN), R55.2
GPIO48: IC10.B7 (GPIO(48)/ETH_1_MII_TXD_0), R56.2
GPIO49: IC10.D8 (GPIO(49)/ETH_1_MII_TXD_1), R57.2
GPIO50: IC10.B8 (GPIO(50)/ETH_1_MII_TXD_2), R58.2
GPIO51: IC10.A8 (GPIO(51)/ETH_1_MII_TXD_3), R59.2
GPIO58: IC10.F13 (GPIO(58)/ETH_MDC), R60.2
GPIO59: IC10.E13 (GPIO(59)/ETH_MDIO), R61.2
GPIO83: IC10.B16 (GPIO(83)/GTM_082), R67.2
GPIO84: IC10.B17 (GPIO(84)/GTM_083), R68.2
GPIO90: IC10.A18 (GPIO(90)/DSPI_2_PCS1), R62.2
GPIO106: IC10.B28 (GPIO(106)/QSPI_1_DATA_A_0), R71.1
GPIO107: IC10.B29 (GPIO(107)/QSPI_1_DATA_A_3), R74.1
GPIO108: IC10.A29 (GPIO(108)/QSPI_1_CS_A0), R78.1
GPIO109: IC10.A30 (GPIO(109)/QSPI_1_DATA_A_4), R75.1
GPIO110: IC10.E28 (GPIO(110)/QSPI_1_DATA_A_1), R72.1
GPIO111: IC10.F25 (GPIO(111)/QSPI_1_DQS_A), R77.1
GPIO112: IC10.B30 (GPIO(112)/QSPI_1_DATA_A_7), R76.1
GPIO114: IC10.E26 (GPIO(114)/!QSPI_1_CK_A), R70.1
GPIO116: IC10.D29 (GPIO(116)/QSPI_1_DATA_A_2), R73.1
GPIO118: IC10.D28 (GPIO(118)/QSPI_1_CS_A1), R79.1
GPIO120: IC10.B24 (GPIO(120)/LIN_6_TX), R82.1
GPIO122: IC10.F22 (GPIO(122)/GTM_121), R69.2
GPIO123: IC10.E22 (GPIO(123)/LIN_7_TX), R83.1
GPIO124: IC10.D22 (GPIO(124)/LIN_7_RX), R84.1
GPIO125: IC10.E23 (GPIO(125)/LIN_8_TX), R85.1
GPIO127: IC10.B25 (GPIO(127)/CAN_12_TX), R89.1
GPIO128: IC10.A25 (GPIO(128)/CAN_12_RX), R90.1
GPIO134: IC10.A27 (GPIO(134)/SENT_1_CH5), R91.1
GPIO136: IC10.A28 (GPIO(136)/SENT_1_CH7), R92.1
GPIO171: IC10.AF8 (GPIO(171)/TDO), R104.2
GREEN_LED: IC10.E32 (GPIO(145)/QSPI_1_DATA_B_0), R114.1
I2C1_SCL: R68.1; also elsewhere on the board
I2C1_SDA: R67.1; also elsewhere on the board
I2C2_SCL: R69.1; also elsewhere on the board
I2C2_SDA: R83.2; also elsewhere on the board
JCOMP: IC10.AG8 (JCOMP), R97.1, R98.2
JRSTN: CN2.7, R128.2
JTCK: CN2.6, R137.1
JTDI: CN2.2, R135.1
JTMS: CN2.4, R136.1
LTE_ON: IC10.AF5 (GPIO(8)/FR_0_RXD_A); also elsewhere on the board
M2M_NET_IND: IC10.AG11 (GPIO(159)/CAN_9_TX); also elsewhere on the board
M2M_PWR_ON: IC10.AF11 (GPIO(160)/CAN_9_RX); also elsewhere on the board
M2M_RSTN: IC10.AG10 (GPIO(161)/GTM_160); also elsewhere on the board
unnamed: R112.2, R113.2, R123.1
unnamed: R107.2, R108.2, R125.1
unnamed: LED2.A, R109.2
unnamed: LED3.A, R114.2
unnamed: LED4.A, R115.2
unnamed: R110.2, R111.2, R124.1
unnamed: C250.1, IC11.3 (SENSE), R118.2, R127.1
unnamed: C258.1, IC11.5 (CT)
unnamed: C248.1, R116.1, Y1.1 (Q_1)
unnamed: LED5.A, R117.2
unnamed: LED6.A, R119.2
unnamed: R105.2, R106.2, R126.1
ORANGE_LED: IC10.D32 (GPIO(141)/QSPI_1_DATA_B_2), R117.1
ORIN_OFF: IC10.U5 (GPIO(18)/GTM_018); also elsewhere on the board
POST_AN: IC10.AD5 (POST_AN), TP7.P$1
RED_LED: IC10.C31 (GPIO(119)/!QSPI_1_INTA), R109.1
RTK_STAT: IC10.P2 (GPIO(30)/GTM_030); also elsewhere on the board
S32_GPI: IC10.B27 (GPIO(135)/SENT_1_CH6); also elsewhere on the board
S32_GPO: R91.2; also elsewhere on the board
SD0_CLK: CN1.5 (CLK/SCLK), R77.2
SD0_CMD: CN1.3 (DI/CMD), R71.2, R129.1
SD0_D0: CN1.7 (DO/DAT0), R74.2, R134.1
SD0_D1: CN1.8 (NC/DAT1), R78.2, R133.1
SD0_D2: CN1.1 (NC/DAT2), R75.2, R131.1
SD0_D3: CN1.2 (CS/CD/DAT3), R72.2, R130.1
SHUT_REQ: IC10.A16 (GPIO(82)/GTM_081); also elsewhere on the board
SPI3_CS0: R88.2; also elsewhere on the board
SPI3_MISO: IC10.J5 (GPIO(32)/GTM_032); also elsewhere on the board
SPI3_MOSI: R66.1; also elsewhere on the board
SPI3_SCK: R65.1; also elsewhere on the board
SPI5_CS1: R73.2; also elsewhere on the board
SPI5_CS3: R79.2; also elsewhere on the board
SPI5_MISO: IC10.F26 (GPIO(113)/QSPI_1_CK_A); also elsewhere on the board
SPI5_MOSI: R76.2; also elsewhere on the board
SPI5_SCK: R70.2; also elsewhere on the board
SPI7_CS0: R90.2; also elsewhere on the board
SPI7_CS1: R84.2; also elsewhere on the board
SPI7_CS2: R92.2; also elsewhere on the board
SPI7_MISO: IC10.D23 (GPIO(126)/LIN_8_RX); also elsewhere on the board
SPI7_MOSI: R89.2; also elsewhere on the board
SPI7_SCK: R85.2; also elsewhere on the board
TCK: IC10.AH8 (GPIO(173)/TCK), R96.2, R137.2
TDI: IC10.AG7 (GPIO(170)/TDI), R93.1, R135.2
TDO: CN2.1, R94.1, R104.1
TIMEPULSE: IC10.E1 (GPIO(36)/CAN_4_TX); also elsewhere on the board
TMS: IC10.AH7 (GPIO(172)/TMS), R95.1, R136.2
UART0_RX: IC10.AH5 (GPIO(1)/LIN_0_RX); also elsewhere on the board
UART0_TX: R80.2; also elsewhere on the board
UART1_RX: IC10.AH4 (GPIO(3)/LIN_1_RX); also elsewhere on the board
UART1_TX: R81.2; also elsewhere on the board
UART3_RX: IC10.B18 (GPIO(91)/DSPI_2_PCS2); also elsewhere on the board
UART3_TX: R62.1; also elsewhere on the board
VSUP_TST: IC10.AE13 (VSUP_TST), TP8.P$1
WHITE_LED: IC10.C32 (GPIO(140)/QSPI_1_DATA_B_3), R119.1
XTAL: C249.1, IC10.N4 (XTAL), Y1.3 (Q_3)

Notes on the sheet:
Debug LEDs
SD Card
JTAG
Crystal
Reset
40MHz
BASIC/design/LM.sch
hw_LM/BASIC
1010xx
jcc5
abs8
S32 Signals
Open Drain
